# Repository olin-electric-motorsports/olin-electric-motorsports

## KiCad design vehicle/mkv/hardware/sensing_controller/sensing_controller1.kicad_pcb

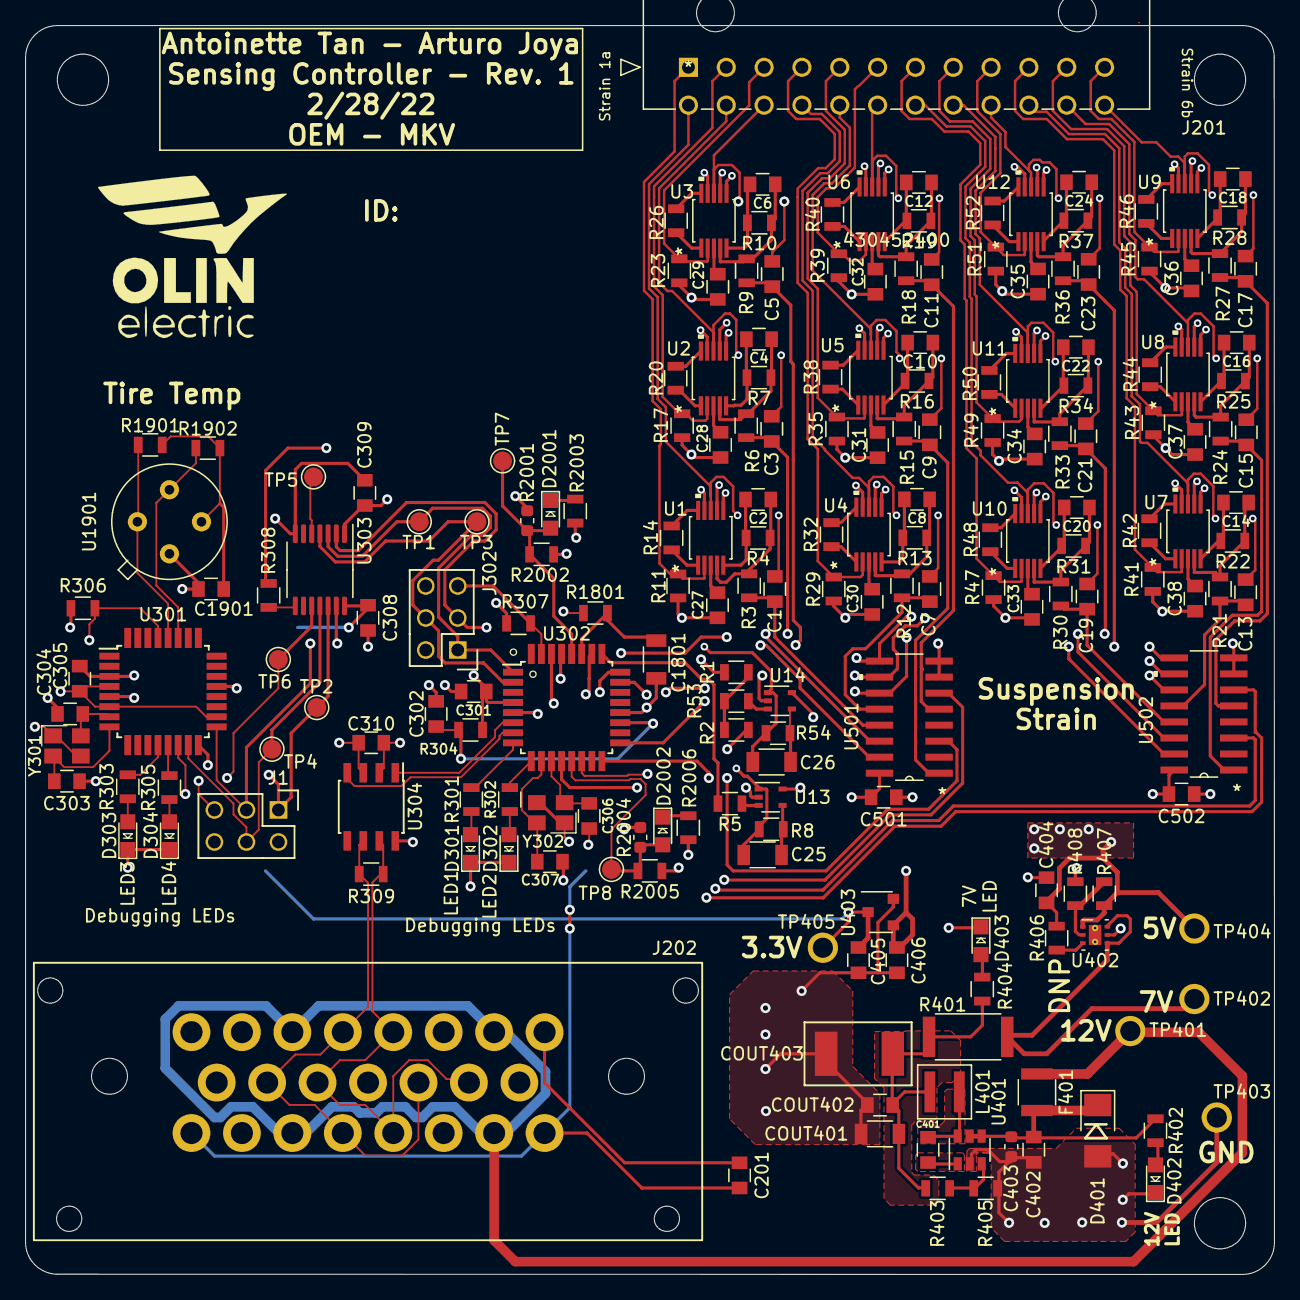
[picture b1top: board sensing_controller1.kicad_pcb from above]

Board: 4 copper layers, 99.0 x 99.0 mm, 196 parts (0 on the bottom side), 162 nets.

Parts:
C1, C3, C5, C7, C9, C11, C13, C15, C17, C19, C21, C23: C_1uF; C_0805_OEM
C2, C4, C6, C8, C10, C12, C14, C16, C18, C20, C22, C24, C302: C_100pF; C_0805_OEM
C25, C26: C_10nF; C_1206_OEM
C27, C28, C29, C30, C31, C32, C33, C34, C35, C36, C37, C38, C201, C301, C305, C308, C309, C310, C401, C402, C405, C406, C501, C502, C1901: C_0.1uF; C_0805_OEM
C303, C304, C306, C307: C_30pF; C_0805_OEM
C403: C_2.2uF; C_0603_1608Metric
C404: C_47uF; C_0805_OEM
C1801: C_22uF; C_1206_OEM
COUT401: C_22uF; C_1206_OEM
COUT402: C_47uF; C_0805_OEM
COUT403: C_33uF; Fuse_1812
D301, D302, D303, D304, D402, D403, D2001, D2002: LED_0805; LED_0805_OEM
D401: D_Zener_18V; DO-214AA
F401: F_500mA_16V; Fuse_1210
J1, J302: CONN_02X03; Pin_Header_Straight_2x03
J201: MicroFit_24; Molex_Microfit3_Header_02x12_Straight_0444322401_OEM
J202: Ampseal_23_RA; Ampseal_23
L401: IND_XAL4020_4X4_COC; XGL4020-822MEC
R1, R2, R11, R17, R23, R29, R35, R39, R41, R43, R45, R47, R49, R51: R_120_05; R_0805_OEM
R3, R6, R9, R12, R15, R18, R21, R24, R27, R30, R33, R36, R304: R_100; R_0805_OEM
R4, R7, R10, R13, R16, R19, R22, R25, R28, R31, R34, R37: R_1.18M; R_0805_OEM
R5, R8, R53, R54, R306, R307, R308, R406, R2002, R2005: R_10K; R_0805_OEM
R14, R20, R26, R32, R38, R40, R42, R44, R46, R48, R50, R52: R_3.92k; R_0805_OEM
R301, R302, R303, R305, R404, R2003, R2006: R_200; R_0805_OEM
R309: R_120_DNP; R_0805_OEM
R401: R_0_2512; R_2512_OEM
R402: R_1K; R_0805_OEM
R403: R_90k; R_0805_OEM
R405: R_15k; R_0805_OEM
R407: R_300K; R_0805_OEM
R408: R_100K; R_0805_OEM
R1801: R_1K_0.1; R_0805_OEM
R1901, R1902: R_4.7K; R_0805_OEM
R2001, R2004: R_0; R_0603_1608Metric
TP1, TP2, TP3, TP4, TP5, TP6, TP7, TP8: Test_Point_SMD; TestPoint_Pad_D1.5mm
TP401, TP402, TP403, TP404, TP405: TP; tp_1.6mm
U1, U2, U3, U4, U5, U6, U7, U8, U9, U10, U11, U12: RM_10_ADI; AD8553ARMZ-REEL
U13, U14: MCP6001T-I-LT; SOT-353_SC-70-5
U301: ATmega328P-AU; TQFP-32_7x7mm_P0.8mm
U302: ATMEGA16M1; TQFP-32_7x7mm_Pitch0.8mm
U303: TXB0104; TSSOP-14_4.4x5mm_P0.65mm
U304: MCP2561-E_SN; SOIC-8_3.9x4.9mm_Pitch1.27mm_OEM
U401: TPS560430YF; SOT-23-6_OEM
U402: DRV0006A; TPS7A2625DRVR
U403: LM3480; SOT-23-3_OEM
U501, U502: 74HC4051; CD74HC4050M96
U1901: MLX90621ESF-BAB-000-TU
Y301, Y302: Crystal_SMD; Crystal_SMD_FA238

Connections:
3.3V: C305.1, C308.2, C405.1, C1901.1, J1.2, R306.1, R1901.2, R1902.1, TP405.1 (TP), U301.4 (VCC), U301.6 (VCC), U301.18 (AVCC), U303.14 (VCCB), U403.1 (VO), U1901.3 (VDD)
5V: C27.2, C28.2, C29.2, C30.2, C31.2, C32.2, C33.2, C34.2, C35.2, C36.2, C37.2, C38.2, C201.2, C301.1, C309.1, C310.1, C404.1, C406.1, C501.2, C502.2, J202.1, J202.8, J302.2, R1.1, R11.1, R17.1, R23.1, R29.1, R35.1, R39.1, R41.1, R43.1, R45.1, R47.1, R49.1, R51.1, R304.1, R307.2, R308.2, R406.2, R407.1, R2001.1, R2004.1, TP404.1 (TP), U1.6 (ENABLE), U2.6 (ENABLE), U3.6 (ENABLE), U4.6 (ENABLE), U5.6 (ENABLE), U6.6 (ENABLE), U7.6 (ENABLE), U8.6 (ENABLE), U9.6 (ENABLE), U10.6 (ENABLE), U11.6 (ENABLE), U12.6 (ENABLE), U13.5 (V+), U14.5 (V+), U302.4 (VCC), U303.1 (VCCA), U304.3 (VDD), U402.1, U403.2 (VI), U501.16 (VCC), U502.16 (VCC)
7V: R401.1, TP402.1 (TP), U402.4, U402.6
12V: F401.2, J202.2, J202.6, J202.17, J202.21, TP401.1 (TP)
/micros/CAN_RX: U302.7 ((PCINT11/T1/ICP1B/RXCAN)PC3), U304.4 (RXD)
/micros/CAN_TX: U302.6 ((PCINT10/T0/TXCAN)PC2), U304.1 (TXD)
/micros/PM_CS: TP5.1, U303.5 (A4)
/micros/PM_MISO: J302.1, TP1.1, U302.1 ((PCINT18/PSCIN2/OC1A/MISO_A)PD2), U303.3 (A2)
/micros/PM_MOSI: J302.4, TP3.1, U302.2 ((PCINT19/TXD/TXLIN/OC0A/~SS/MOSI_A)PD3), U303.4 (A3)
/micros/PM_RESET: J302.5, R307.1, U302.31 ((PCINT24/OCD/~RESET)PE0)
/micros/PM_SCK: J302.3, U302.12 ((PCINT20/ADC1/RXD/RXLIN/ICP1A/SCK_A)PD4), U303.2 (A1)
/micros/SM_CS: TP6.1, U301.14 ((PCINT2/~SS/OC1B)PB2), U303.10 (B4)
/micros/SM_MISO: J1.1, TP2.1, U301.16 ((PCINT3/MISO)PB4), U303.12 (B2)
/micros/SM_MOSI: J1.4, TP4.1, U301.15 ((PCINT3/OC2A/MOSI)PB3), U303.11 (B3)
/micros/SM_RESET: J1.5, R306.2, U301.29 ((~RESET/PCINT14)PC6)
/micros/SM_SCK: J1.3, U301.17 ((SCK/PCINT5)PB5), U303.13 (B1)
/suspension_strain/STRAIN_1A_OUT: C1.1, R3.2, U501.13 (A0)
/suspension_strain/STRAIN_1B_OUT: C19.1, R30.2, U502.13 (A0)
/suspension_strain/STRAIN_2A_OUT: C3.1, R6.2, U501.14 (A1)
/suspension_strain/STRAIN_2B_OUT: C21.1, R33.2, U502.14 (A1)
/suspension_strain/STRAIN_3A_OUT: C5.1, R9.2, U501.15 (A2)
/suspension_strain/STRAIN_3B_OUT: C23.1, R36.2, U502.15 (A2)
/suspension_strain/STRAIN_4A_OUT: C7.1, R12.2, U501.12 (A3)
/suspension_strain/STRAIN_4B_OUT: C13.1, R21.2, U502.12 (A3)
/suspension_strain/STRAIN_5A_OUT: C9.1, R15.2, U501.1 (A4)
/suspension_strain/STRAIN_5B_OUT: C15.1, R24.2, U502.1 (A4)
/suspension_strain/STRAIN_6A_OUT: C11.1, R18.2, U501.5 (A5)
/suspension_strain/STRAIN_6B_OUT: C17.1, R27.2, U502.5 (A5)
CAN+: J202.4, J202.10, J202.13, J202.19, R309.1, U304.7 (CANH)
CAN-: J202.5, J202.11, J202.14, J202.20, R309.2, U304.6 (CANL)
FRONT_SENSE: D2001.2 (A), R2001.2, R2002.1, TP7.1, U302.28 ((PCINT7/ADC4/SCK/PSCOUT0B)PB7)
GND: C201.1, C301.2, C302.2, C303.2, C304.2, C305.2, C306.2, C307.2, C308.1, C309.2, C310.2, C402.1, C403.2, C404.2, C405.2, C406.2, C501.1, C502.1, C1801.2, C1901.2, COUT401.1, COUT402.2, COUT403.2, D301.1 (K), D302.1 (K), D303.1 (K), D304.1 (K), D401.2 (A), D402.1 (K), D403.1 (K), J1.6, J202.3, J202.7, J202.12, J202.16, J202.18, J202.22, J202.23, J302.6, R2.2, R405.2, R408.2, R2002.2, R2003.2, R2005.2, R2006.2, TP403.1 (TP), U13.2 (V-), U14.2 (V-), U301.3 (GND), U301.5 (GND), U301.21 (GND), U302.5 (GND), U302.20 (AGND), U303.7 (GND), U304.2 (VSS), U304.8 (STBY), U401.2 (GND), U402.5, U403.3 (GND), U501.7 (VEE), U501.8 (GND), U502.7 (VEE), U502.8 (GND), U1901.4 (GND), Y301.2, Y301.4, Y302.2, Y302.4
HALL_EFFECT_SENSE: J202.9, U302.14 ((PCINT22/ADC3/INT0/ACMPN2)PD6)
LEFT_SENSE: D2002.2 (A), R2004.2, R2005.1, TP8.1, U302.13 ((PCINT21/ADC2/ACMP2)PD5)
LIN_POT_SENSE: J202.15, R1801.1
LIN_POT_SENSE_FILTERED: C1801.1, R1801.2, U302.27 ((PCINT6/ADC7/PSCOUT1B)PB6)
unnamed: C2.1, R3.1, R4.1, U1.4 (VO)
unnamed: C2.2, R4.2, U1.5 (VFB)
unnamed: C4.1, R6.1, R7.1, U2.4 (VO)
unnamed: C4.2, R7.2, U2.5 (VFB)
unnamed: C6.1, R9.1, R10.1, U3.4 (VO)
unnamed: C6.2, R10.2, U3.5 (VFB)
unnamed: C8.1, R12.1, R13.1, U4.4 (VO)
unnamed: C8.2, R13.2, U4.5 (VFB)
unnamed: C10.1, R15.1, R16.1, U5.4 (VO)
unnamed: C10.2, R16.2, U5.5 (VFB)
unnamed: C12.1, R18.1, R19.1, U6.4 (VO)
unnamed: C12.2, R19.2, U6.5 (VFB)
unnamed: C14.1, R21.1, R22.1, U7.4 (VO)
unnamed: C14.2, R22.2, U7.5 (VFB)
unnamed: C16.1, R24.1, R25.1, U8.4 (VO)
unnamed: C16.2, R25.2, U8.5 (VFB)
unnamed: C18.1, R27.1, R28.1, U9.4 (VO)
unnamed: C18.2, R28.2, U9.5 (VFB)
unnamed: C20.1, R30.1, R31.1, U10.4 (VO)
unnamed: C20.2, R31.2, U10.5 (VFB)
unnamed: C22.1, R33.1, R34.1, U11.4 (VO)
unnamed: C22.2, R34.2, U11.5 (VFB)
unnamed: C24.1, R36.1, R37.1, U12.4 (VO)
unnamed: C24.2, R37.2, U12.5 (VFB)
unnamed: C25.2, R8.2, U13.4 (-)
unnamed: C26.2, R54.2, U14.4 (-)
unnamed: C27.1, U1.3 (VCC)
unnamed: C28.1, U2.3 (VCC)
unnamed: C29.1, U3.3 (VCC)
unnamed: C30.1, U4.3 (VCC)
unnamed: C31.1, U5.3 (VCC)
unnamed: C32.1, U6.3 (VCC)
unnamed: C33.1, U10.3 (VCC)
unnamed: C34.1, U11.3 (VCC)
unnamed: C35.1, U12.3 (VCC)
unnamed: C36.1, U9.3 (VCC)
unnamed: C37.1, U8.3 (VCC)
unnamed: C38.1, U7.3 (VCC)
unnamed: C302.1, R304.2, U302.19 (AVCC)
unnamed: C303.1, U301.8 ((PCINT7/XTAL2/TOSC2)PB7), Y301.1
unnamed: C304.1, U301.7 ((PCINT6/XTAL1/TOSC1)PB6), Y301.3
unnamed: C306.1, U302.11 ((PCINT26/ADC0/XTAL2)PE2), Y302.1
unnamed: C307.1, U302.10 ((PCINT25/OC0B/XTAL1)PE1), Y302.3
unnamed: C401.1, L401.1, U401.6 (SW)
unnamed: C401.2, U401.1 (CB)
unnamed: C402.2, C403.1, D401.1 (K), F401.1, R402.1, U401.4 (EN), U401.5 (VIN)
unnamed: COUT401.2, COUT402.1, COUT403.1, L401.2, R401.2, R403.1, R404.1
unnamed: D301.2 (A), R301.1
unnamed: D302.2 (A), R302.1
unnamed: D303.2 (A), R303.1
unnamed: D304.2 (A), R305.1
unnamed: D402.2 (A), R402.2
unnamed: D403.2 (A), R404.2
unnamed: D2001.1 (K), R2003.1
unnamed: D2002.1 (K), R2006.1
unnamed: R1.2, R2.1, R53.2
unnamed: R5.1, U13.3 (+)
unnamed: R14.1, U1.10 (RGB)
unnamed: R14.2, U1.1 (RGA)
unnamed: R20.1, U2.10 (RGB)
unnamed: R20.2, U2.1 (RGA)
unnamed: R26.1, U3.10 (RGB)
unnamed: R26.2, U3.1 (RGA)
unnamed: R32.1, U4.10 (RGB)
unnamed: R32.2, U4.1 (RGA)
unnamed: R38.1, U5.10 (RGB)
unnamed: R38.2, U5.1 (RGA)
unnamed: R40.1, U6.10 (RGB)
unnamed: R40.2, U6.1 (RGA)
unnamed: R42.1, U7.10 (RGB)
unnamed: R42.2, U7.1 (RGA)
unnamed: R44.1, U8.10 (RGB)
unnamed: R44.2, U8.1 (RGA)
unnamed: R46.1, U9.10 (RGB)
unnamed: R46.2, U9.1 (RGA)
unnamed: R48.1, U10.10 (RGB)
unnamed: R48.2, U10.1 (RGA)
unnamed: R50.1, U11.10 (RGB)
unnamed: R50.2, U11.1 (RGA)
unnamed: R52.1, U12.10 (RGB)
unnamed: R52.2, U12.1 (RGA)
unnamed: R53.1, U14.3 (+)
unnamed: R301.2, U302.8 ((PCINT0/MISO/PSCOUT2A)PB0)
unnamed: R302.2, U302.9 ((PCINT1/MOSI/PSCOUT2B)PB1)
unnamed: R303.2, U301.12 ((PCINT0/CLKO/ICP1)PB0)
unnamed: R305.2, U301.13 ((PCINT1/OC1A)PB1)
unnamed: R308.1, U303.8 (OE)
unnamed: R403.2, R405.1, U401.3 (FB)
unnamed: R407.2, R408.1, U402.2
SM_SCL: R1901.1, U301.28 ((ADC5/SCL/PCINT13)PC5), U1901.1 (SCL)
SM_SDA: R1902.2, U301.27 ((ADC4/SDA/PCINT12)PC4), U1901.2 (SDA)
STRAIN_1A_+: J201.1, R11.2, U1.2 (VINP)
STRAIN_1A_-: C1.2, J201.13, U1.8 (GND)
STRAIN_1B_+: J201.7, R47.2, U10.2 (VINP)
STRAIN_1B_-: C19.2, J201.19, U10.8 (GND)
STRAIN_2A_+: J201.2, R17.2, U2.2 (VINP)
STRAIN_2A_-: C3.2, J201.14, U2.8 (GND)
STRAIN_2B_+: J201.8, R49.2, U11.2 (VINP)
STRAIN_2B_-: C21.2, J201.20, U11.8 (GND)
STRAIN_3A_+: J201.3, R23.2, U3.2 (VINP)
STRAIN_3A_-: C5.2, J201.15, U3.8 (GND)
STRAIN_3B_+: J201.9, R51.2, U12.2 (VINP)
STRAIN_3B_-: C23.2, J201.21, U12.8 (GND)
STRAIN_4A_+: J201.4, R29.2, U4.2 (VINP)
STRAIN_4A_-: C7.2, J201.16, U4.8 (GND)
STRAIN_4B_+: J201.10, R41.2, U7.2 (VINP)
STRAIN_4B_-: C13.2, J201.22, U7.8 (GND)
STRAIN_5A_+: J201.5, R35.2, U5.2 (VINP)
STRAIN_5A_-: C9.2, J201.17, U5.8 (GND)
STRAIN_5B_+: J201.11, R43.2, U8.2 (VINP)
STRAIN_5B_-: C15.2, J201.23, U8.8 (GND)
STRAIN_6A_+: J201.6, R39.2, U6.2 (VINP)
STRAIN_6A_-: C11.2, J201.18, U6.8 (GND)
STRAIN_6B_+: J201.12, R45.2, U9.2 (VINP)
STRAIN_6B_-: C17.2, J201.24, U9.8 (GND)
STRAIN_MUX1_OUT: U302.16 ((PCINT2/ADC5/INT1/ACMPN0)PB2), U501.3 (A)
STRAIN_MUX2_OUT: U302.26 ((PCINT5/ADC6/INT2/ACMPN1/AMP2-)PB5), U502.3 (A)
STRAIN_S0: U302.29 ((PCINT16/PSCOUT0A)PD0), U501.11 (S0), U502.11 (S0)
STRAIN_S1: U302.17 ((PCINT12/ADC8/ACMPN3/AMP1-)PC4), U501.10 (S1), U502.10 (S1)
STRAIN_S2: U302.23 ((PCINT3/AMP0-)PB3), U501.9 (S2), U502.9 (S2)
STRAIN_VOLTAGE_REF_2BUFFER: R5.2, U302.25 ((PCINT15/D2A/AMP2+)PC7)
STRAIN_VOLTAGE_REF_2INAMP: C25.1, R8.1, U1.7 (VREF), U2.7 (VREF), U3.7 (VREF), U4.7 (VREF), U5.7 (VREF), U6.7 (VREF), U7.7 (VREF), U8.7 (VREF), U9.7 (VREF), U10.7 (VREF), U11.7 (VREF), U12.7 (VREF), U13.1
Vpg: R406.1, U402.3
WHEATSTONE_OUT_-: C26.1, R54.1, U1.9 (VINN), U2.9 (VINN), U3.9 (VINN), U4.9 (VINN), U5.9 (VINN), U6.9 (VINN), U7.9 (VINN), U8.9 (VINN), U9.9 (VINN), U10.9 (VINN), U11.9 (VINN), U12.9 (VINN), U14.1
nSTRAIN_MUX1_EN: U302.24 ((PCINT4/AMP0+)PB4), U501.6 (~E)
nSTRAIN_MUX2_EN: U302.30 ((PCINT8/INT3/PSCOUT1A)PC0), U502.6 (~E)

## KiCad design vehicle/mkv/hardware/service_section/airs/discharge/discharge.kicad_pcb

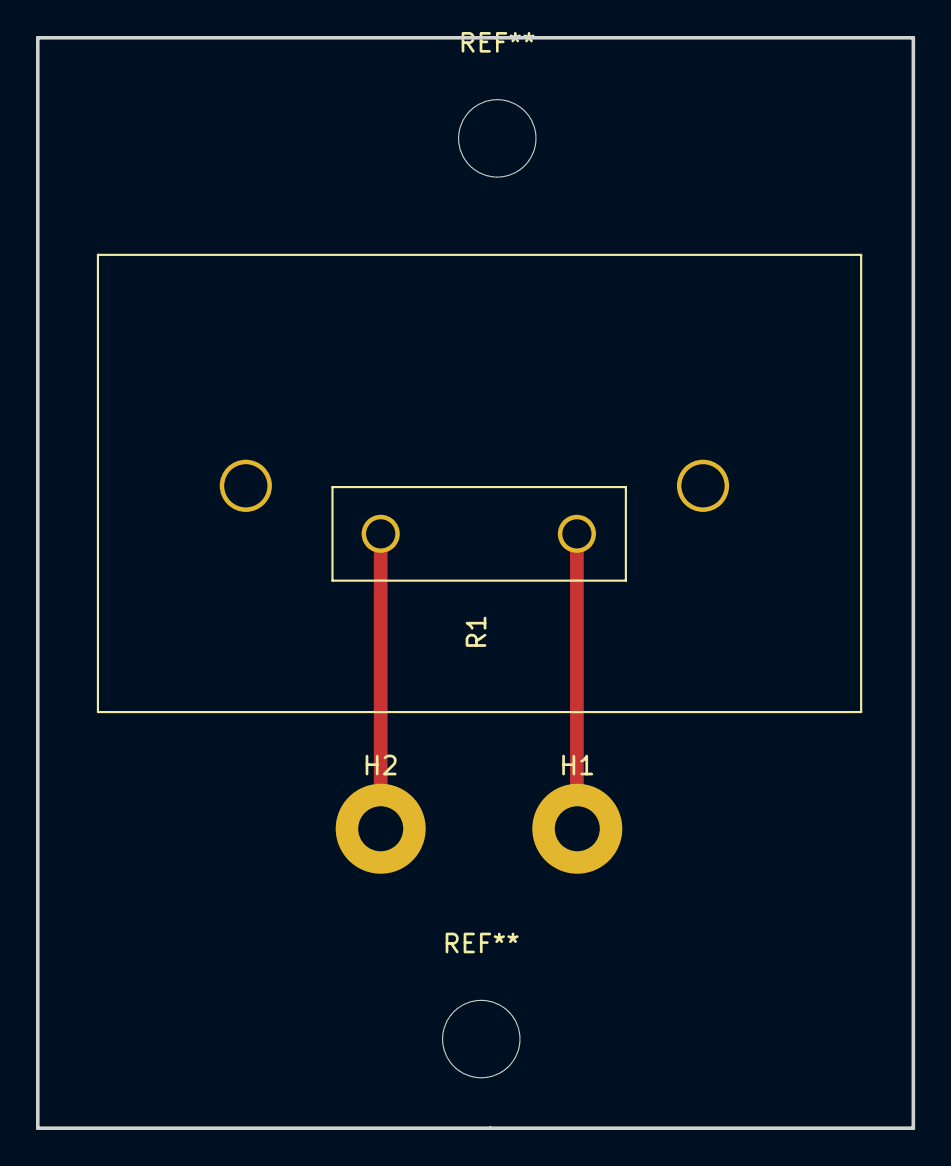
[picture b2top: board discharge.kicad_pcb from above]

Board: 2 copper layers, 48.6 x 60.6 mm, 3 parts (0 on the bottom side), 2 nets.

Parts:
H1, H2: MountingHole_Pad; MountingHole_2.5mm_Pad
R1: R_3K_HS; R_3k_HS_TO247

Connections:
unnamed: H1.1, R1.2
unnamed: H2.1, R1.1

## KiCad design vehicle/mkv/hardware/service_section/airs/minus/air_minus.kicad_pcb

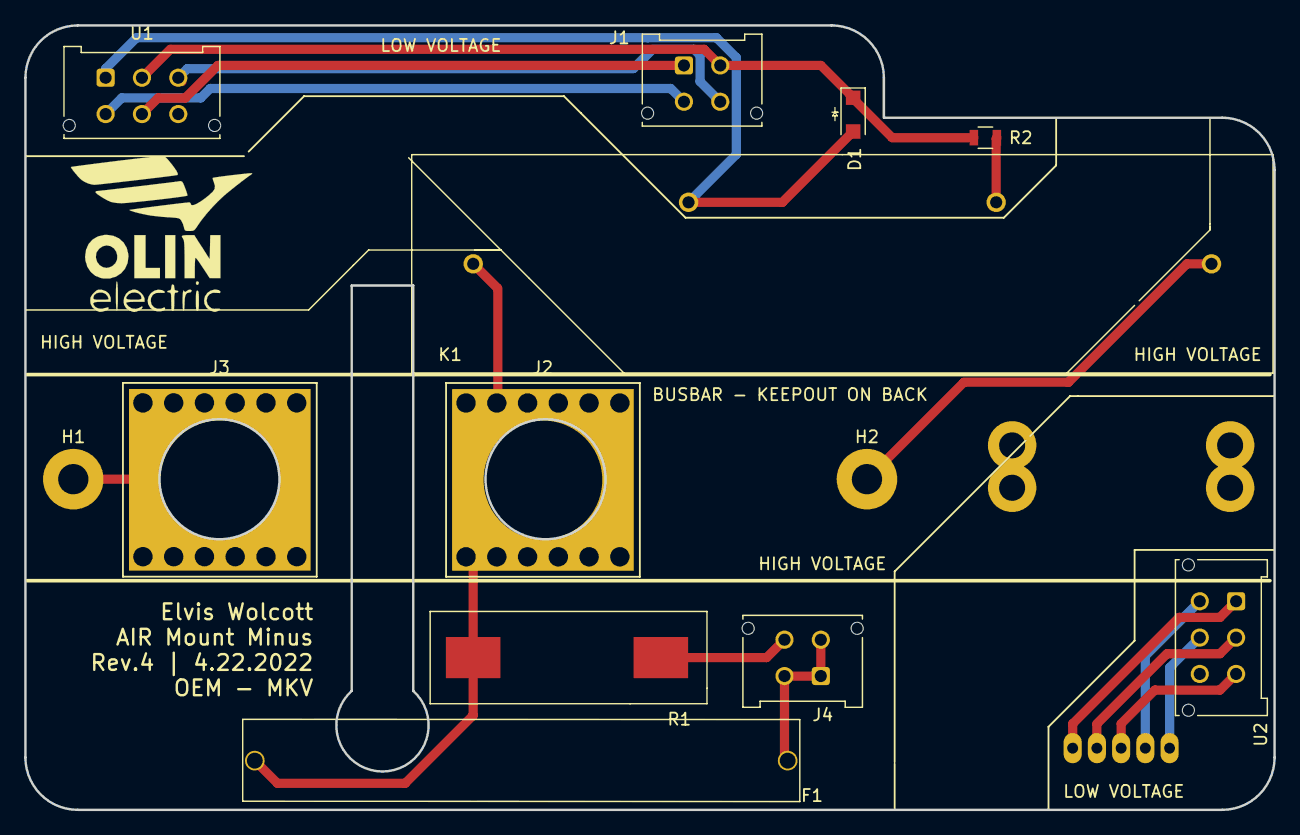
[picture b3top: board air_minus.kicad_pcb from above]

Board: 2 copper layers, 103.1 x 64.8 mm, 14 parts (1 on the bottom side), 16 nets.

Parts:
D1: SS110LW; D_SOD-123W_OEM
F1: F_1A_600V; Fuse_1A_600V
H1, H2: HOLE; MountingHole_2.5mm_Pad
J1, J4: MicroFit_VT_4
J2, J3: redcude_7461166; redcube_7461166
K1: 5503-12-1(NO); Relay_Coto_5500
R1: R_15K_HV; R_TSMP_SMD_5329
R2: R_12; R_0805_OEM
U1, U2: MicroFit_VT_6
U3: HO_60_250-p0100

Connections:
/AIR-_AUX+: J1.4, U1.3
/AIR-_AUX-: J1.3, U1.4
/AIR-_LSD: J1.1, U1.5
/FINAL_SHUTDOWN: D1.1, J1.2, R2.2, U1.2
/GND: U2.2, U3.2
/HV_BAT-: H1.1, J3.1
/HV_BSPD_CURRENT_SENSOR: F1.2, J4.1, J4.2, J4.3
/HV_TS-: F1.1, J2.1, K1.4, R1.2
/HV_TSMP-: J4.4, R1.1
/OCD: U2.5, U3.5
/PRECHARGE_LSD: D1.2, K1.3, U1.1
/UC+: U2.1, U3.1
/Vout: U2.3, U3.3
/Vref: U2.4, U3.4
unnamed: H2.1, K1.1
unnamed: K1.2, R2.1

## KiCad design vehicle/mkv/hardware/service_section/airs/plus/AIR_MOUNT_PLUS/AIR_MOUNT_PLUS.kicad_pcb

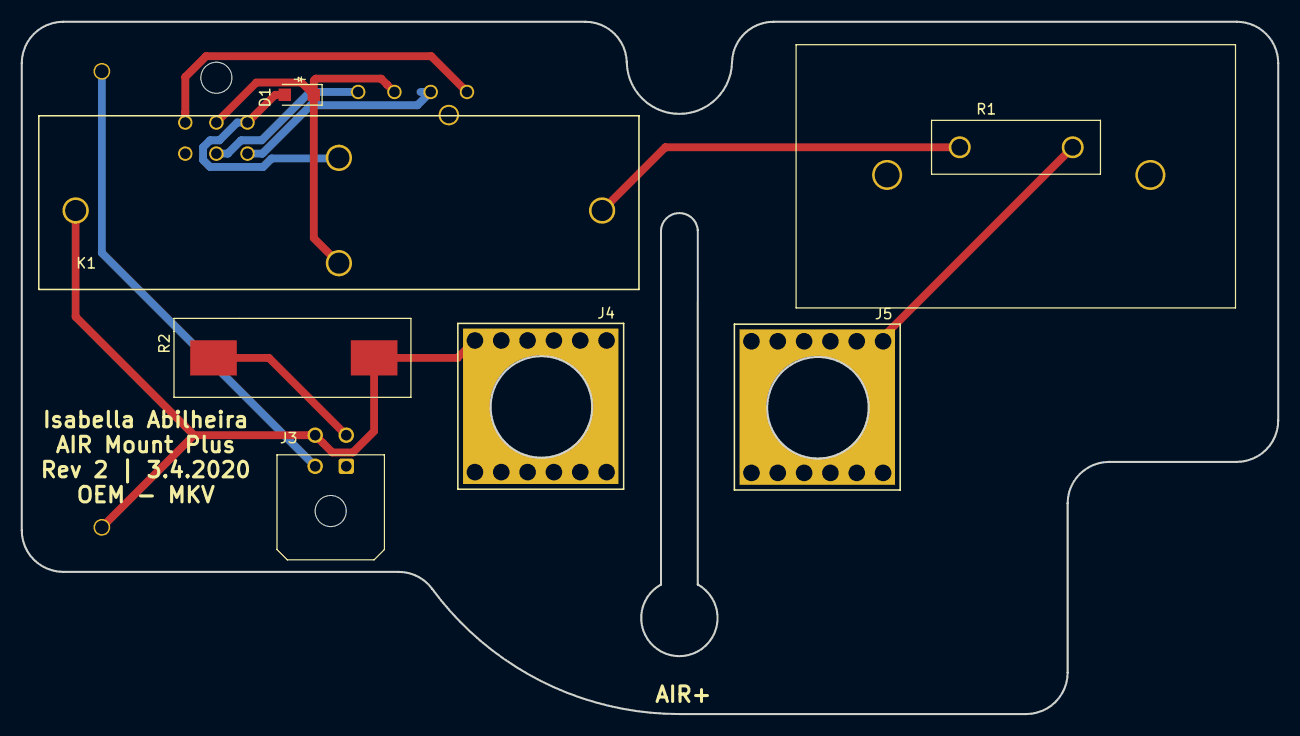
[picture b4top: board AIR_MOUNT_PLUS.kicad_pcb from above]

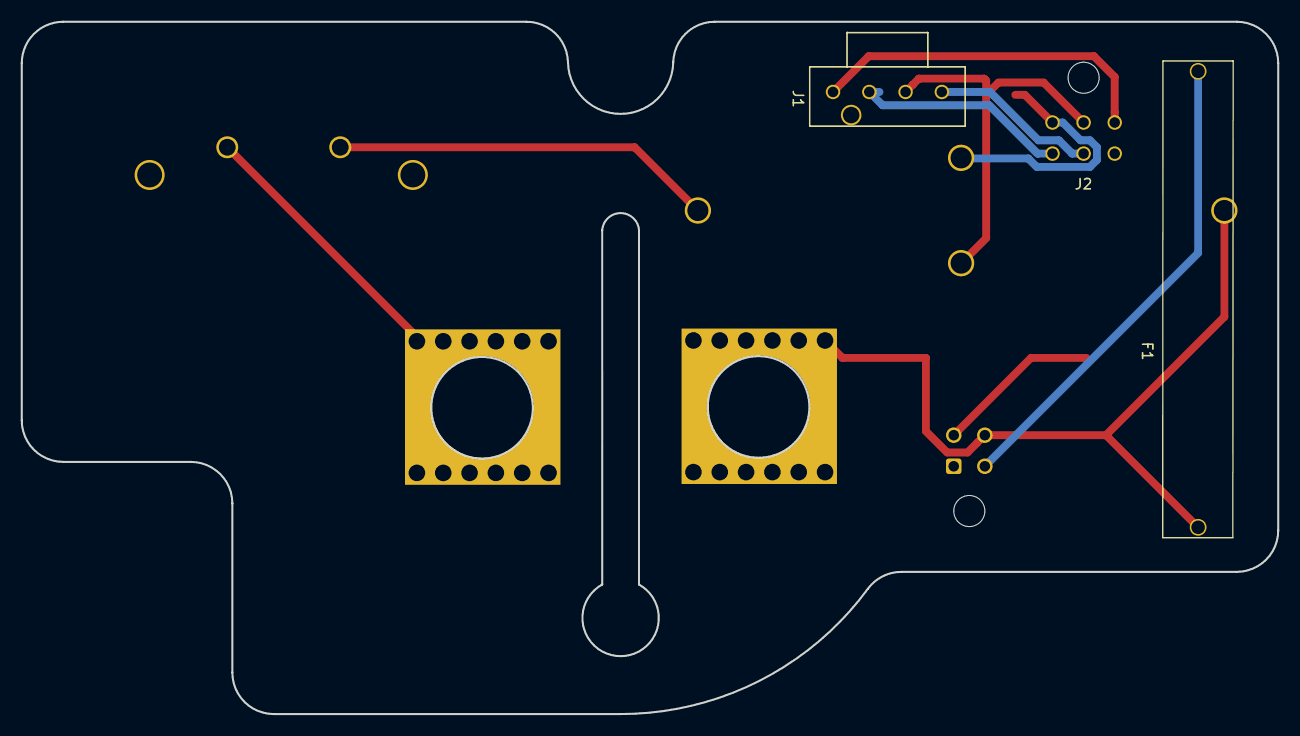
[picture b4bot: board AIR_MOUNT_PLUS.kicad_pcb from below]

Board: 2 copper layers, 121.2 x 66.8 mm, 10 parts (3 on the bottom side), 10 nets.

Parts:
D1: SS110LW; D_SOD-123W_OEM
F1: F_1A_600V; Fuse_1A_600V
J1: UF_4_VT; Ultrafit_4
J2: MicroFit_RA_06
J3: MicroFit_RA_4
J4, J5: redcude_7461166; redcube_7461166
K1: DBR71210(NC); D-Series_Cynergy_Relay
R1: R_3K_HS; R_3k_HS_TO247
R2: R_10K_HV; R_TSMP_SMD_5329

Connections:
/AUX+: J1.1, J2.3
/AUX-: J1.2, J2.4
/BAT-: J5.1, R1.1
/Coil+: D1.1, J1.3, J2.2, K1.4
/Coil-: J1.4, J2.5
/GND: D1.2, J2.1, K1.3
/TS-: F1.1, J3.4, J4.1, K1.1, R2.2
/TSMP-: J3.3, R2.1
/TS_Fused-: F1.2, J3.2
unnamed: K1.2, R1.2

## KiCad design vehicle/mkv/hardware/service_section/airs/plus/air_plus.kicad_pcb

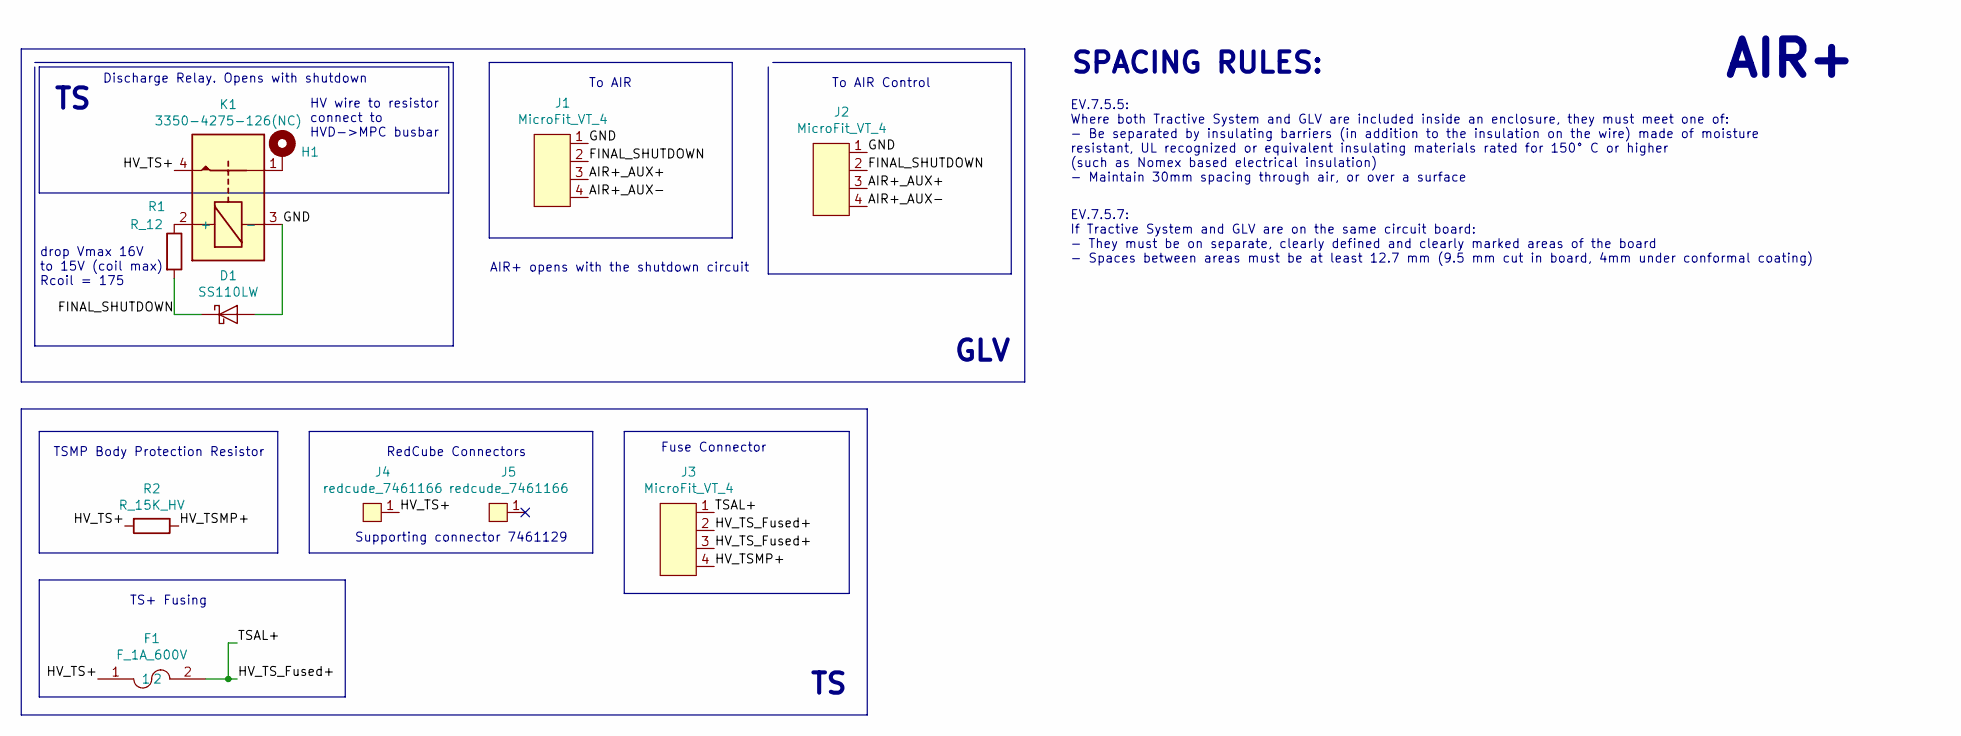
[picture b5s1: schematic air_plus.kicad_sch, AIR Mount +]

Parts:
D1: SS110LW; D_SOD-123W_OEM; MPN SS110LWRVGCT-ND
F1: F_1A_600V; Fuse_1A_600V
H1: MountingHole_Pad; MountingHole_2.5mm_Pad
J1, J2, J3: MicroFit_VT_4; MPN 430450414
J4, J5: redcude_7461166; redcube_7461166
K1: 3350-4275-126(NC); Relay_Comus_3350; MPN 3350-4275-126
R1: R_12; R_0805_OEM; MPN CPF-A-0805B12RE
R2: R_15K_HV; R_TSMP_SMD_5329; MPN SMF515KJT

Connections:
/AIR+_AUX+: J1.3, J2.3
/AIR+_AUX-: J1.4, J2.4
/FINAL_SHUTDOWN: D1.1 (K), J1.2, J2.2, R1.2
/GND: D1.2 (A), J1.1, J2.1, K1.3 (-)
/HV_TS+: F1.1, J4.1, K1.4, R2.2
/HV_TSMP+: J3.4, R2.1
/HV_TS_Fused+: F1.2, J3.1, J3.2, J3.3
unnamed: H1.1, K1.1
unnamed: K1.2 (+), R1.1

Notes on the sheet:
drop Vmax 16V to 15V (coil max) Rcoil = 175
HV wire to resistor connect to HVD->MPC busbar
AIR+
AIR+ opens with the shutdown circuit
EV.7.5.7: If Tractive System and GLV are on the same circuit board: - They must be on separate, clearly defined and clearly marked areas of the board - Spaces between areas must be at least 12.7 mm (9.5 mm cut in board, 4mm under conformal coating)
Supporting connector 7461129
To AIR
GLV
SPACING RULES:
Fuse Connector
To AIR Control
Discharge Relay. Opens with shutdown
TS+ Fusing
RedCube Connectors
TSMP Body Protection Resistor
EV.7.5.5: Where both Tractive System and GLV are included inside an enclosure, they must meet one of: - Be separated by insulating barriers (in addition to the insulation on the wire) made of moisture resistant, UL recognized or equivalent insulating materials rated for 150° C or higher (such as No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

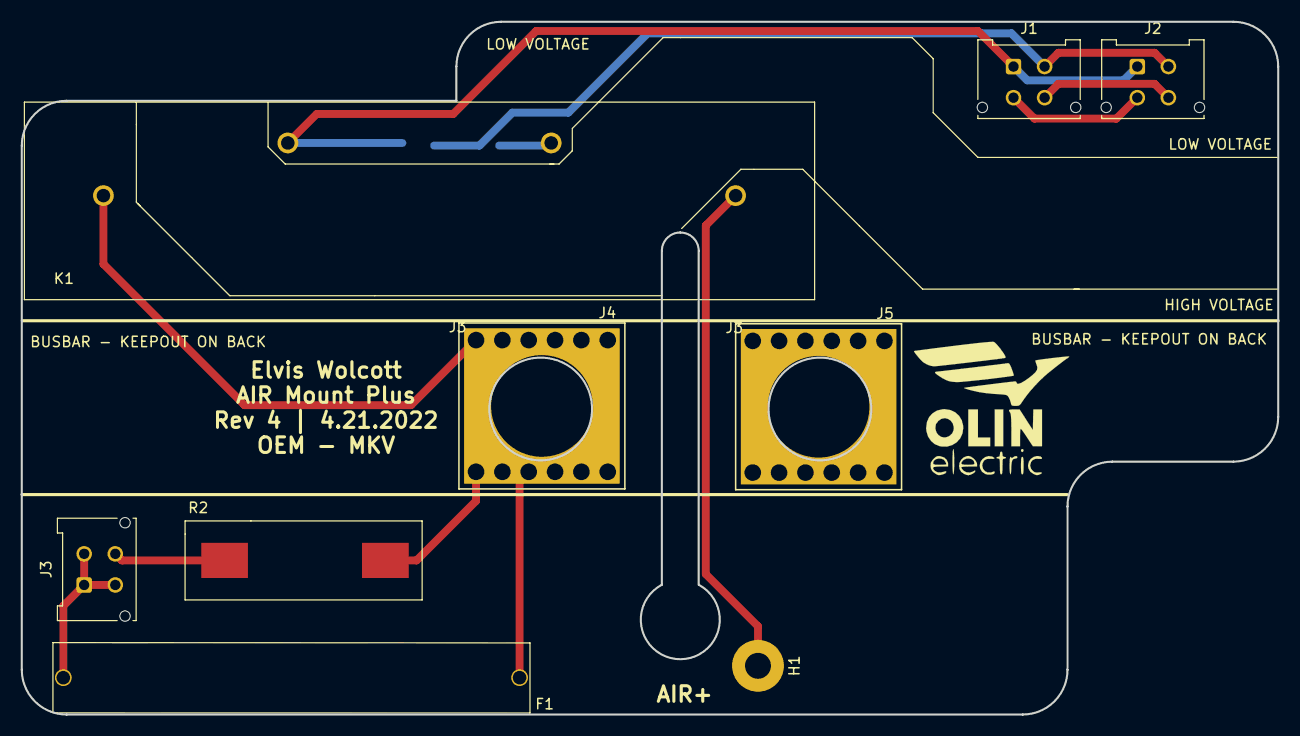
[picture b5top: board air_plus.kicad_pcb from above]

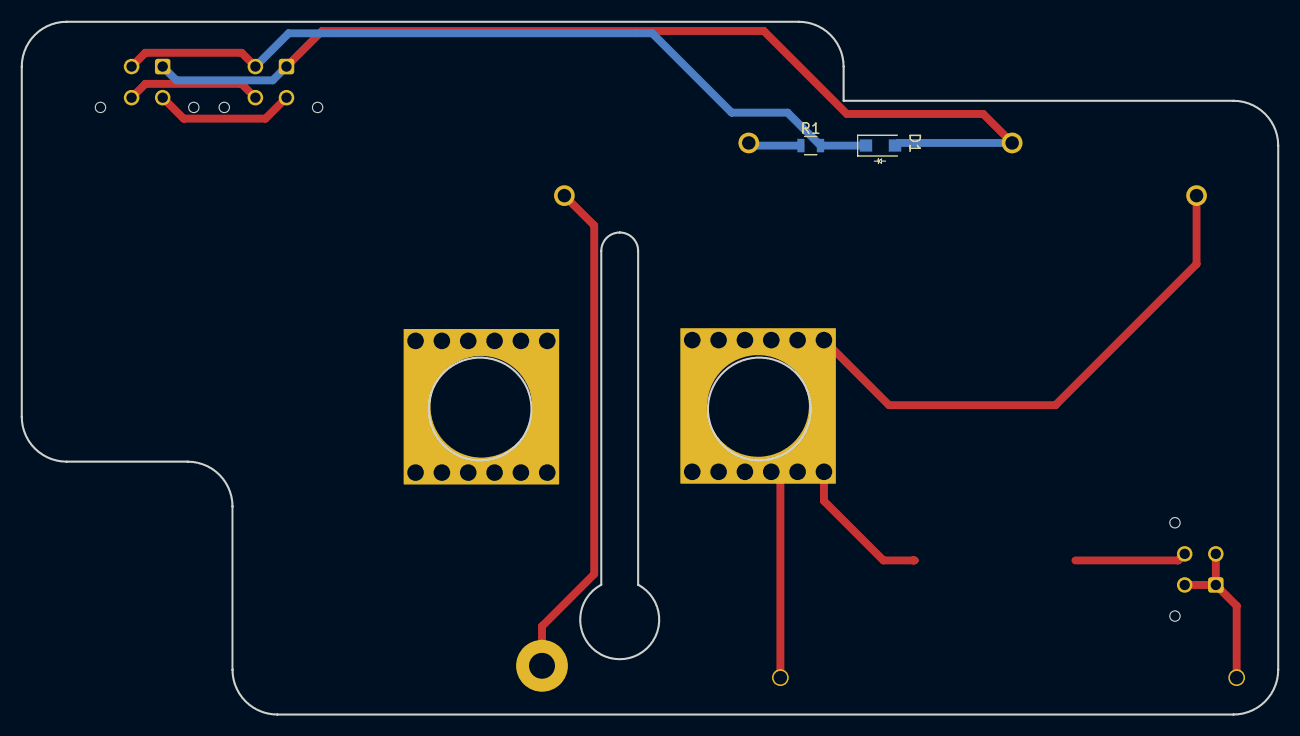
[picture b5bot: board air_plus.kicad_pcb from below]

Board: 2 copper layers, 121.2 x 66.8 mm, 11 parts (2 on the bottom side), 9 nets.

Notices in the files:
parts and their libraries:
Copyright 2021 Accelerated Designs. All rights reserved.
